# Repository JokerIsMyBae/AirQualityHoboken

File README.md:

# AirQualityHoboken
Applied IoT project voor luchtkwaliteitsmetingen in Hobokense Polder

### Doel
Meten van specifieke luchtkwaliteitsparameters:
- CO2
- TVOC
- NOx
- Fijnstof
- Temperatuur
- Luchtvochtigheid
- Luchtdruk

### To-Do:
- Bouwen van een sensorbord
- Meten van specifieke luchtkwaliteitsparameters
- Werkt op batterij & PV-cel
- Locatie via GPS
- PCB
- Communicatie via LoRaWAN
- Langdurige test op statische plaatsen Hoboken
- Data opslagen in een DB

### Deliverables
- Robuuste werkende schakeling
- Versie voor Hoboken / light-weight autonome versie voor PoAB
- Sensorbord, modulair, met LoRaWAN module
- 2 testversies op de campus
- 10 definitieve versies

### Deliverables
- Implementatie in Hoboken op statische plaatsen
- Implementatie in de haven op statische plaatsen
- Implementatie in op een drone
- Communicatie via LoRaWAN
- Visualisatie van data via NodeRed - Grafana
- PCB
- Documentatie
- Film

References:
- Power delivery (DFRobot + solar panels)
  https://github.com/Verbeast2K/zanzi-doc/tree/master/sensorbox
- Other parts
  https://github.com/Jappie3/zanzi-doc

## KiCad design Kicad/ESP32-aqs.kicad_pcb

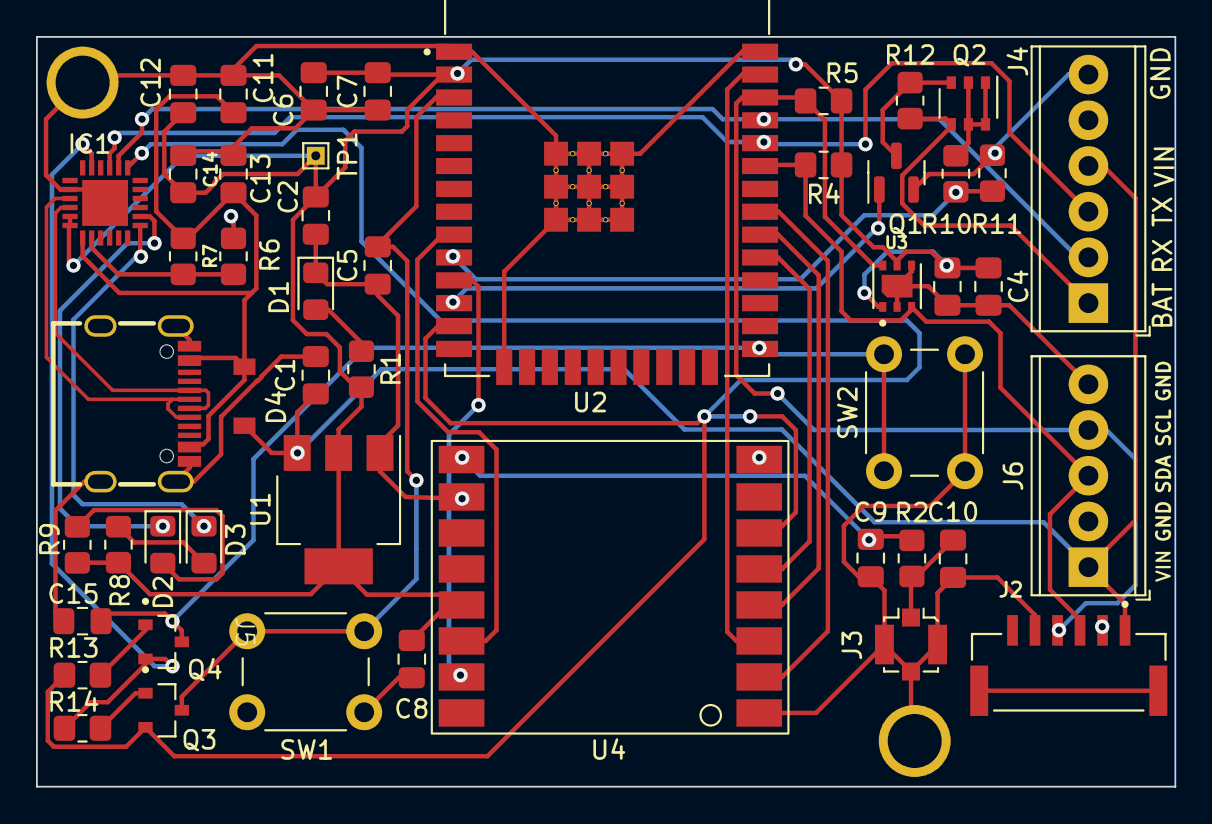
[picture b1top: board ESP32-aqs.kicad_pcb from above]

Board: 2 copper layers, 63.2 x 41.7 mm, 51 parts (0 on the bottom side), 35 nets.

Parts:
C1, C8: 100nF; C_0805_2012Metric_Pad1.18x1.45mm_HandSolder
C2, C6, C13: 10µF; C_0805_2012Metric_Pad1.18x1.45mm_HandSolder
C3, C4, C9, C10: 1µF; C_0805_2012Metric_Pad1.18x1.45mm_HandSolder
C5, C7, C11, C12, C14, C15: 0.1µF; C_0805_2012Metric_Pad1.18x1.45mm_HandSolder
D1, D2, D3: LED; LED_0805_2012Metric_Pad1.15x1.40mm_HandSolder
D4: D_Schottky; SOD-123FL
H1, H2: MountingHole_Pad; MountingHole_2.2mm_M2_ISO7380_Pad
IC1: CP2102N-A02-GQFN24; QFN50P400X400X80-25N
J2: JST connector SEN55; JST_BM06B-GHS-TBT_LF__SN__N_
J3: ufl connector; U.FL_Molex_MCRF_73412-0110_Vertical
J4: UART Connector; TerminalBlock_Phoenix_MPT-0,5-6-2.54_1x06_P2.54mm_Horizontal
J5: USB-TYPE-C-018
J6: test point / jst connector; TerminalBlock_Phoenix_MPT-0,5-5-2.54_1x05_P2.54mm_Horizontal
Q1: IRLML0030; SOT-23
Q2: PMN48XP; TSOP-6_1.65x3.05mm_P0.95mm
Q3, Q4: SS8050-G; TRANS_SS8050-G
R1, R8, R9: 1k; R_0805_2012Metric_Pad1.20x1.40mm_HandSolder
R2, R4, R5: 4k7; R_0805_2012Metric_Pad1.20x1.40mm_HandSolder
R6: 20k; R_0805_2012Metric_Pad1.20x1.40mm_HandSolder
R7: 47k; R_0805_2012Metric_Pad1.20x1.40mm_HandSolder
R10, R11: 100k; R_0805_2012Metric_Pad1.20x1.40mm_HandSolder
R12: 1M; R_0805_2012Metric_Pad1.20x1.40mm_HandSolder
R13, R14: 10k; R_0805_2012Metric_Pad1.20x1.40mm_HandSolder
SW1, SW2: TC-1102-B-C-B; SW_PUSH_6mm
TP1: VDD; TestPoint_THTPad_1.0x1.0mm_Drill0.5mm
U1: LD1117S33TR_SOT223; SOT-223-3_TabPin2
U2: ESP32-WROOM-32; MODULE_ESP32-WROOM-32
U3: SGP41-D-R4; XDCR_SGP41-D-R4
U4: SX1276S8S+T-X1

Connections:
+3V3: C2.1, C3.1, C4.1, C6.1, C7.1, C8.1, C12.1, C14.1, IC1.5 (VIO), IC1.6 (VDD), R1.2, R4.1, R5.1, R8.1, R9.1, TP1.1, U1.2 (VO), U2.2 (3V3), U3.1 (VDD), U3.5 (VDDH), U4.13 (VCC)
ANT: C9.2, R2.1, U4.9 (RF)
BAT: J4.1, Q2.4 (S), R12.1
BOOT: C15.1, Q4.3, SW2.1, U2.25 (IO0)
CS: U2.29 (IO5), U4.5 (NSS)
D+: IC1.3 (D+), J5.A6 (DP1), J5.B6 (DP2)
D-: IC1.4 (D-), J5.A7 (DN1), J5.B7 (DN2)
DIO0: U2.9 (IO33), U4.14 (DIO0)
DIO1: U2.11 (IO26), U4.15 (DIO1)
DTR: IC1.23 (DTR), Q4.2, R14.1
EN: C5.1, Q3.3, SW1.2, U2.3 (EN)
GND: C1.2, C2.2, C3.2, C4.2, C5.2, C6.2, C7.2, C8.2, C9.1, C10.1, C11.2, C12.2, C13.2, C14.2, C15.2, D1.1 (K), H1.1, H2.1, IC1.2 (GND_1), IC1.25 (GND_2), J2.2, J2.5, J3.2 (Ext), J4.6, J5.0 (SH), J5.1 (SH), J5.2 (SH), J5.3 (SH), J5.A1 (GND), J5.A12 (GND), J5.B1 (GND), J5.B12 (GND), J6.2, J6.5, Q1.2 (S), R7.2, R11.2, SW1.1, SW2.2, U1.1 (GND), U2.1 (GND), U2.15 (GND), U2.38 (GND), U2.39_1 (GND), U2.39_2 (GND), U2.39_3 (GND), U2.39_4 (GND), U2.39_5 (GND), U2.39_6 (GND), U2.39_7 (GND), U2.39_8 (GND), U2.39_9 (GND), U2.39_10 (GND), U2.39_11 (GND), U2.39_12 (GND), U2.39_13 (GND), U2.39_14 (GND), U2.39_15 (GND), U2.39_16 (GND), U2.39_17 (GND), U2.39_18 (GND), U2.39_19 (GND), U2.39_20 (GND), U2.39_21 (GND), U3.2 (VSS), U3.4 (N/A), U3.7 (EXP), U4.1 (GND), U4.8 (GND), U4.10 (GND)
MISO: U2.31 (IO19), U4.2 (SO)
MOSI: U2.37 (IO23), U4.3 (SI)
unnamed: D1.2 (A), R1.1
unnamed: D2.2 (A), R9.2
unnamed: D3.2 (A), R8.2
unnamed: IC1.8 (VBUS), R6.2, R7.1
unnamed: C10.2, J3.1 (In), R2.2
unnamed: Q1.3 (D), Q2.3 (G), R12.2
unnamed: Q2.1 (D), Q2.2 (D), Q2.5 (D), Q2.6 (D), R10.1
unnamed: Q3.1, R14.2
unnamed: Q4.1, R13.2
READ_BAT: Q1.1 (G), U2.12 (IO27)
RST: IC1.19 (RTS), Q3.2, R13.1, U2.13 (IO14), U4.6 (RST)
RX: IC1.20 (RXD), J4.2, U2.35 (TXD0)
RXLED: D3.1 (K), IC1.13 (GPIO.1_/_RXT)
SCK: U2.30 (IO18), U4.4 (SCK)
SCL: J2.4, J6.4, R5.2, U2.36 (IO22), U3.6 (SCL)
SDA: J2.3, J6.3, R4.2, U2.33 (IO21), U3.3 (SDA)
TX: IC1.21 (TXD), J4.3, U2.34 (RXD0)
TXLED: D2.1 (K), IC1.14 (GPIO.0_/_TXT)
VBAT: R10.2, R11.1, U2.10 (IO25)
VBUS: C11.1, C13.1, D4.2 (A), IC1.7 (VREGIN), J5.A4 (VBUS), J5.A9 (VBUS), J5.B4 (VBUS), J5.B9 (VBUS), R6.1
VIN: C1.1, D4.1 (K), J2.1, J4.4, J6.1, U1.3 (VI)

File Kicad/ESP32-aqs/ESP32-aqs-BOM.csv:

Comment,Designator,Footprint,LCSC Part Number
100k,R10,R_0805_2012Metric_Pad1.20x1.40mm_HandSolder
100k,R11,R_0805_2012Metric_Pad1.20x1.40mm_HandSolder
4k7,R5,R_0805_2012Metric_Pad1.20x1.40mm_HandSolder
4k7,R2,R_0805_2012Metric_Pad1.20x1.40mm_HandSolder
4k7,R4,R_0805_2012Metric_Pad1.20x1.40mm_HandSolder
1k,R1,R_0805_2012Metric_Pad1.20x1.40mm_HandSolder
1k,R8,R_0805_2012Metric_Pad1.20x1.40mm_HandSolder
1k,R9,R_0805_2012Metric_Pad1.20x1.40mm_HandSolder
PMN48XP,Q2,TSOP-6_1.65x3.05mm_P0.95mm, C552986
CP2102N-A02-GQFN24,IC1,QFN50P400X400X80-25N,C969913
SGP41-D-R4,U3,XDCR_SGP41-D-R4,C3659325
100nF,C1,C_0805_2012Metric_Pad1.18x1.45mm_HandSolder
100nF,C8,C_0805_2012Metric_Pad1.18x1.45mm_HandSolder
LED,D1,LED_0805_2012Metric_Pad1.15x1.40mm_HandSolder
LED,D2,LED_0805_2012Metric_Pad1.15x1.40mm_HandSolder
LED,D3,LED_0805_2012Metric_Pad1.15x1.40mm_HandSolder
ufl connector,J3,U.FL_Molex_MCRF_73412-0110_Vertical
0.1uF,C5,C_0805_2012Metric_Pad1.18x1.45mm_HandSolder
0.1uF,C7,C_0805_2012Metric_Pad1.18x1.45mm_HandSolder
0.1uF,C15,C_0805_2012Metric_Pad1.18x1.45mm_HandSolder
0.1uF,C14,C_0805_2012Metric_Pad1.18x1.45mm_HandSolder
0.1uF,C12,C_0805_2012Metric_Pad1.18x1.45mm_HandSolder
0.1uF,C11,C_0805_2012Metric_Pad1.18x1.45mm_HandSolder
1uF,C4,C_0805_2012Metric_Pad1.18x1.45mm_HandSolder
1uF,C9,C_0805_2012Metric_Pad1.18x1.45mm_HandSolder
1uF,C3,C_0805_2012Metric_Pad1.18x1.45mm_HandSolder
1uF,C10,C_0805_2012Metric_Pad1.18x1.45mm_HandSolder
TC-1102-B-C-B,SW1,SW_PUSH_6mm
TC-1102-B-C-B,SW2,SW_PUSH_6mm
ESP32-WROOM-32,U2,MODULE_ESP32-WROOM-32,C529582
SX1276S8S+T-X1,U4,SX1276S8S+T-X1,C2844472
VDD,TP1,TestPoint_THTPad_1.0x1.0mm_Drill0.5mm
USB4085-GF-A_REVA4,J1,GCT_USB4085-GF-A_REVA4
MountingHole_Pad,H1,MountingHole_2.2mm_M2_ISO7380_Pad
MountingHole_Pad,H2,MountingHole_2.2mm_M2_ISO7380_Pad
JST connector SEN55,J2,JST_BM06B-GHS-TBT_LF__SN__N_,C189892
test point / jst connector,J6,TerminalBlock_Phoenix_MPT-0,5-5-2.54_1x05_P2.54mm_Horizontal
D_Schottky,D4,SOD-123FL,C489144
UART Connector,J4,TerminalBlock_Phoenix_MPT-0,5-6-2.54_1x06_P2.54mm_Horizontal,C474924
47k,R7,R_0805_2012Metric_Pad1.20x1.40mm_HandSolder
10uF,C2,C_0805_2012Metric_Pad1.18x1.45mm_HandSolder
10uF,C6,C_0805_2012Metric_Pad1.18x1.45mm_HandSolder
10uF,C13,C_0805_2012Metric_Pad1.18x1.45mm_HandSolder
10k,R13,R_0805_2012Metric_Pad1.20x1.40mm_HandSolder
10k,R14,R_0805_2012Metric_Pad1.20x1.40mm_HandSolder
SS8050-G,Q3,TRANS_SS8050-Gn,C164885
SS8050-G,Q4,TRANS_SS8050-G,C164885
IRLML0030,Q1,SOT-23
1M,R12,R_0805_2012Metric_Pad1.20x1.40mm_HandSolder
20k,R6,R_0805_2012Metric_Pad1.20x1.40mm_HandSolder
LD1117S33TR_SOT223,U1,SOT-223-3_TabPin2,C86781

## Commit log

2023-09-21 Kicad Schematics and PCB
2023-09-21 Blokschema v1
2023-09-21 Create Componentenlijst.docx
    Added componentlist
2023-09-21 start power consumption
2023-09-21 power consumption
2023-09-21 Initial commit on branch
2023-09-21 LoRa sketch
    First communication with the things network
2023-09-28 Update schematic
2023-09-28 fix: edited includepath settings for pio src
2023-09-28 chore: updated includepath
2023-09-28 pcb design
2023-09-28 Refactoring LoRaWAN (TTN) code
    Removed the screen and all its credentials.
    Removed old code in void loop/setup
2023-09-28 feat: created sen55 example usage
2023-09-28 Add box enclosure concept
2023-09-28 feat: renamed and added serial print of results
2023-09-28 feat: created sgp example usage
2023-09-28 PCB design update
2023-09-28 DEV board + lora shield
    the needed library for the lora shield + example code
2023-10-05 chore: copied sgp example to main
2023-10-05 Update main.ino
    Test code = werkt
2023-10-05 docs: added docs to sgp41 example
2023-10-05 chore: deleted outdated
2023-10-05 refactor: created measurement loop function
2023-10-05 docs: added comments to example sketch
2023-10-05 PCB + BoM
2023-10-12 feat: created pio project for embedded code
2023-10-12 chore: deleted unused files
2023-10-12 chore: updated gitignore
2023-10-12 fix: ino to cpp and h for proper imports
2023-10-12 refactor: added in measurementloop()
2023-10-12 feat: added lora band settings
2023-10-19 added node-red flow and docker compose
2023-10-19 PCB design geupdate
2023-10-26 added ansible playbook
2023-10-26 fix: edited baud rate for functioning serial
2023-10-26 feat: put sen55example in main
2023-10-26 fix: new include
2023-10-26 comments: edited comment
2023-10-26 fix: set proper baud rate
2023-10-26 feat: edited for sen55
2023-10-26 refactor: fill txBuffer with for loop
2023-10-26 test-validatie toegevoegd
2023-10-26 test validatie.md
2023-10-26 update test-validatie
2023-10-26 fix: removed double data array
2023-10-26 chore: updated .gitignore
2023-11-16 troubleshoot sen 55
2023-11-16 schematic v2
2023-11-16 main fixed
    16/11
2023-11-16 Added aansluit pictures
2023-11-16 chore: update gitignore
2023-11-16 feat: add config file
2023-11-16 refactor: make read_meas non blocking
2023-11-16 feat: add deep sleep
2023-11-16 PCB v2
2023-11-16 silkscreen aanpassing
2023-11-16 feat: add axp chip code back
2023-11-16 feat: add library for axp
2023-11-22 sounds
2023-11-23 fix: commented unused channels
2023-11-23 AXP removed
    removed AXP module, GPS and all serial.prints
2023-11-23 chore: remove random line
2023-11-23 chore: update dir structure
2023-11-23 feat: create lmic lib test
2023-11-23 chore: delete unused file
2023-11-23 fix: setup of otaa conn
2023-11-23 chore: remove credentials
2023-11-23 chore: remove unused libs
2023-11-23 fix: fix everything and add otaa
2023-11-23 chore: add monitor filters
2023-11-23 feat: add constants for sleep
2023-11-23 feat: add sleep test
2023-11-26 Added 3d print files for roof
2023-11-30 chore: update dependencies
2023-11-30 docs: clarify sleep_ms
2023-11-30 fix: sleep_ms correction
2023-11-30 Update Documentatie.docx
    added layout
2023-11-30 feat: add esp deep sleep to loop
2023-11-30 fix: change from ms to sleep_s
2023-11-30 fix: forgot to start measurement
2023-11-30 updated schematic
2023-11-30 pcb update
2023-12-07 chore: update minor things
2023-12-07 PCB v3
2023-12-07 eerste versie sgp41 aangepast
2023-12-07 chore: add debugging
2023-12-07 refactor: put debug functions in lib
2023-12-07 comment: explain different parts of code
2023-12-07 fix: try to resolve tx error automatically
2023-12-07 chore: add versions to libdeps
2023-12-07 comment: explain sensor_setup_s
2023-12-14 refactor: handle send error by going back to sleep
2023-12-14 PCB 2de versie
2023-12-14 Adde lastest roofbox updates
2023-12-14 feat: fix lora getting stuck in polling opmode
2023-12-14 verbruik
2023-12-21 fix: remove unnecessary comma
2023-12-21 Backplate final version
2023-12-21 Added latest node-red flow added latest docker-compose
2024-01-09 update doc
2024-01-10 add doc pdf version
